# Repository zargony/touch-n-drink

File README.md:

# Touch 'n Drink

Touch 'n Drink is a small device that reads NFC id cards of club members of the [Aeroclub (LSC) Hamm][LSC Hamm] and allows to pay for items like cold drinks offered at the clubhouse. Purchases are forwarded to accounting so members pay via their regular monthly invoices. We're located at airfield [EDLH] in Hamm, Germany.

## Features

- Fetches authorized users and list of articles for sale from [Vereinsflieger] API
- Allows users to identify with NFC tag or id card and purchase articles
- Optional event tracking using [Mixpanel] for usage analytics
- Connects to 2.4 GHz WPA2/WPA3 Wifi (IPv4, DHCP)
- Simple numeric keypad and large, bright OLED display
- Power supply using standard USB-C cable (PD not required)
- Ergonomically priced and widely available hardware components
- Magnetic wall mount

## Hardware

ESP32-C3, Keypad, OLED Display and NFC reader in a custom acrylic case. See [hardware] folder for details.

## PCB

Small custom PCB for the microcontroller and connectors to other components. Either manufactured or manually soldered to a perfboard. See [pcb] folder for details.

## Firmware

Written in [Rust]. See [firmware] folder for details.

## Contributions

If you like this project, want to use it at your club, or if you want to discuss ideas and suggestions, feel free to start a [discussion][discussions] or open an [issue][issues]. Feel free to fork this repository and base your work upon it. Please open a pull request if your changes or features are useful to a broad audience.

## License

Hardware licensed under the [CERN Open Hardware License (Strongly Reciprocal)][OHL]. Software licensed under the [European Union Public License (EUPL)][EUPL]. Unless you explicitly state otherwise, any contribution intentionally submitted for inclusion in the work by you, shall be licensed as above, without any additional terms or conditions.

[hardware]: ./hardware
[firmware]: ./firmware
[pcb]: ./pcb

[discussions]: https://github.com/zargony/touch-n-drink/discussions
[issues]: https://github.com/zargony/touch-n-drink/issues

[EDLH]: https://skyvector.com/airport/EDLH/Hamm-Lippewiesen-Airport
[EUPL]: https://interoperable-europe.ec.europa.eu/collection/eupl/eupl-text-eupl-12
[LSC Hamm]: https://flugplatz-hamm.de
[Mixpanel]: https://mixpanel.com
[OHL]: https://cern-ohl.web.cern.ch/home
[Rust]: https://www.rust-lang.org
[Vereinsflieger]: https://www.vereinsflieger.de

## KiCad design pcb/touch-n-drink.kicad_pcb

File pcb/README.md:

# Touch 'n Drink PCB

## Custom PCB

A custom PCB holds the ESP32-C3 Module, a buzzer and connectors to wire up display, keypad and NFC reader. The PCB is quite simple and easy to manufacture. Choose any manufacturer you like.

If you don't want to manufacture a PCB, it's also easily possible to wire up components on a perfboard (see below).

Soldered PCB:

Empty PCB:

Rendered PCB model:

PCB Layout:

### Components

- 60x40 mm custom 2-layer PCB
- 1x ESP32-C3 SuperMini
  ([AliExpress](https://s.click.aliexpress.com/e/_DdYM4t9)) <!-- https://www.aliexpress.com/item/1005005967641936.html -->
  ([Amazon](https://amzn.to/4bCXYxz)) <!-- https://www.amazon.de/iHaospace-ESP32-C3-Mini-Entwicklungboard-ESP32-C3FN4/dp/B0D1Y5CPLX -->
  ([Model](https://grabcad.com/library/esp32c3-supermini-1))
- 1x Passive buzzer, THT, 12085
- 1x S8550, SMT, TSOT-23 (or other generic NPN transistor, BEC pin ordering)
- 1x 1k resistor, SMT, 0805
- 2x 5k resistor, SMT, 0805
- 1x 4-pin JST PH header, SMT, horizontal, S4B-PH-SM4-TB
- 1x 5-pin JST PH header, SMT, horizontal, S5B-PH-SM4-TB
- 1x 7-pin JST PH header, SMT, horizontal, S7B-PH-SM4-TB

## Perfboard (optional, instead of PCB)

Instead of manufacturing a custom PCB, you can wire up components on a 60x40 mm perfboard.

### Components

- Prototype PCB 60x40
  ([AliExpress](https://s.click.aliexpress.com/e/_Ddm12Wr)) <!-- https://www.aliexpress.com/item/1005006665029598.html -->
  ([Amazon](https://amzn.to/4eYnoIY)) <!-- https://www.amazon.de/Akozon-Leiterplatte-Doppelseiten-Prototyping-Universal/dp/B0B3MJ3WJM -->
  ([Model](https://grabcad.com/library/pcb-prototype-60x40-1))
- ESP32-C3 SuperMini
  ([AliExpress](https://s.click.aliexpress.com/e/_DdYM4t9)) <!-- https://www.aliexpress.com/item/1005005967641936.html -->
  ([Amazon](https://amzn.to/4bCXYxz)) <!-- https://www.amazon.de/iHaospace-ESP32-C3-Mini-Entwicklungboard-ESP32-C3FN4/dp/B0D1Y5CPLX -->
  ([Model](https://grabcad.com/library/esp32c3-supermini-1))
- Passive buzzer module, 3.3V, active low
  ([AliExpress](https://s.click.aliexpress.com/e/_Dl2FWF1)) <!-- https://www.aliexpress.com/item/1005006316591026.html -->
  ([Amazon](https://amzn.to/3Y72Ibw)) <!-- https://www.amazon.de/Jopto-Passives-niedrigstufiges-Lautsprecher-Kompatibel/dp/B096ZWCG7F -->
  ([Model](https://grabcad.com/library/buzzer-module-fc-07-1))
- Connectors for wiring to front panel (optional)
- Wires for soldering

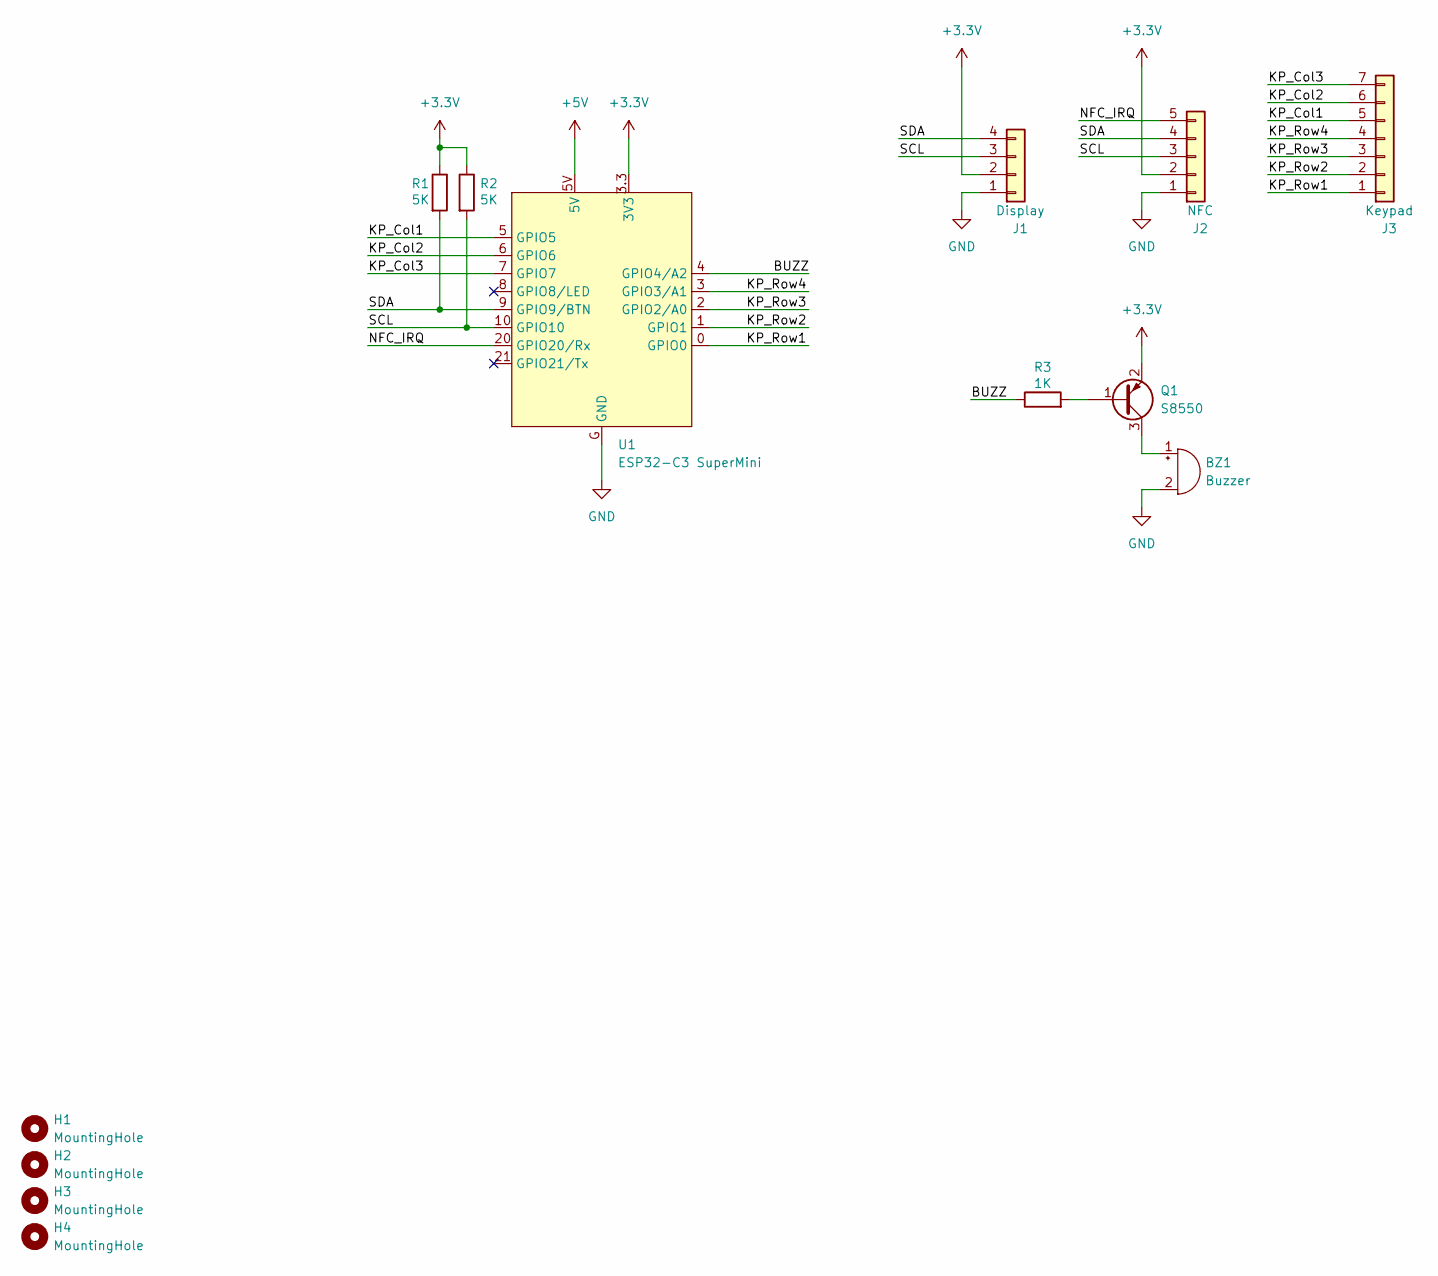
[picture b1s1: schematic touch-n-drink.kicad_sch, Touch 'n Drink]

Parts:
BZ1: Buzzer; MagneticBuzzer_ProSignal_ABT-410-RC
H1, H2, H3, H4: MountingHole; MountingHole_2.2mm_M2
J1: Display; JST_PH_S4B-PH-SM4-TB_1x04-1MP_P2.00mm_Horizontal
J2: NFC; JST_PH_S5B-PH-SM4-TB_1x05-1MP_P2.00mm_Horizontal
J3: Keypad; JST_PH_S7B-PH-SM4-TB_1x07-1MP_P2.00mm_Horizontal
Q1: S8550; TSOT-23
R1, R2: 5K; R_0805_2012Metric_Pad1.20x1.40mm_HandSolder
R3: 1K; R_0805_2012Metric_Pad1.20x1.40mm_HandSolder
U1: ESP32-C3 SuperMini; ESP32-C3_SuperMini

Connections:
+3.3V: J1.2, J2.2, Q1.2 (E), R1.1, R2.1, U1.3.3 (3V3)
+5V: U1.5V
/BUZZ: R3.1, U1.4 (GPIO4/A2)
/KP_Col1: J3.5, U1.5 (GPIO5)
/KP_Col2: J3.6, U1.6 (GPIO6)
/KP_Col3: J3.7, U1.7 (GPIO7)
/KP_Row1: J3.1, U1.0 (GPIO0)
/KP_Row2: J3.2, U1.1 (GPIO1)
/KP_Row3: J3.3, U1.2 (GPIO2/A0)
/KP_Row4: J3.4, U1.3 (GPIO3/A1)
/NFC_IRQ: J2.5, U1.20 (GPIO20/Rx)
/SCL: J1.3, J2.3, R2.2, U1.10 (GPIO10)
/SDA: J1.4, J2.4, R1.2, U1.9 (GPIO9/BTN)
GND: BZ1.2 (-), J1.1, J2.1, U1.G (GND)
unnamed: BZ1.1 (+), Q1.3 (C)
unnamed: Q1.1 (B), R3.2

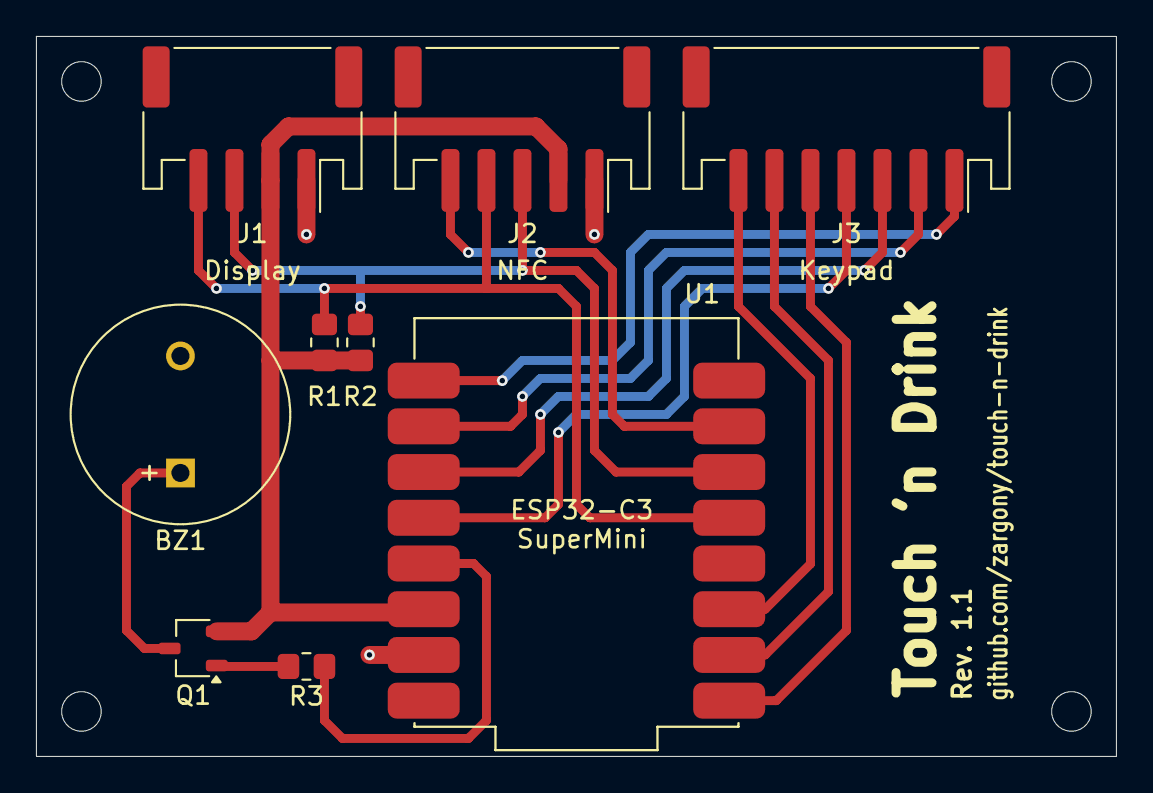
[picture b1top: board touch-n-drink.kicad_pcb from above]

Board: 2 copper layers, 60.0 x 40.0 mm, 13 parts (0 on the bottom side), 15 nets.

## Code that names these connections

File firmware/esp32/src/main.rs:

//! Touch 'n Drink Firmware
//!
//! Pinout ESP32-C3 Super Mini board
//!
//!                               | USB |
//! (Keypad Col1) A5/MISO/GPIO5 -  5 | 5V - 5V
//! (Keypad Col2)    MOSI/GPIO6 -  6 | G  - GND
//! (Keypad Col3)      SS/GPIO7 -  7 | 33 - 3V3
//!   (Board LED)     SDA/GPIO8 -  8 | 4  - GPIO4/A4/SCK (Buzzer)
//!     (I2C SDA)     SCL/GPIO9 -  9 | 3  - GPIO3/A3     (Keypad Row4)
//!     (I2C SCL)        GPIO10 - 10 | 2  - GPIO2/A2     (Keypad Row3)
//!     (NFC IRQ)     RX/GPIO20 - 20 | 1  - GPIO1/A1     (Keypad Row2)
//!                   TX/GPIO21 - 21 | 0  - GPIO0/A0     (Keypad Row1)
//!
//! Pinout OLED 2.42" Display
//!
//!            1   2   3   4
//!           GND VDD SCL SDA
//! GND - 1 |
//! VDD - 2 |
//! SCL - 3 |
//! SDA - 4 |
//!
//! Pinout 3x4 Matrix Keypad
//!
//!  1   2    3    4    5    6    7    8   9
//!  nc Col2 Row1 Col1 Row4 Col3 Row3 Row2 nc
//!
//! Pinout PN532 NFC Module
//!
//!             SCK MISO MOSI SS VCC GND IRQ RSTO
//!              1   2    3   4   5   6   7   8
//! GND - 1 |
//! VCC - 2 |
//! SDA - 3 |
//! SCL - 4 |
//!

#![no_std]
#![no_main]

mod buzzer;
mod config;
mod display;
mod keypad;
mod nfc;
mod pn532;
mod update;
mod wifi;

use alloc::boxed::Box;
use common::{GIT_SHA_STR, VERSION_STR};
use embassy_embedded_hal::shared_bus::asynch::i2c::I2cDevice;
use embassy_executor::Spawner;
use embassy_sync::{blocking_mutex::raw::NoopRawMutex, mutex::Mutex};
use embassy_time::{Duration, Timer};
use esp_backtrace as _;
use esp_hal::clock::CpuClock;
use esp_hal::efuse;
use esp_hal::gpio::{DriveMode, Input, InputConfig, Level, Output, OutputConfig, Pull};
use esp_hal::i2c::master::{BusTimeout, Config as I2cConfig, I2c};
use esp_hal::interrupt::software::SoftwareInterruptControl;
use esp_hal::peripherals::Peripherals;
use esp_hal::rng::Rng;
use esp_hal::rtc_cntl::{Rtc, RwdtStage};
use esp_hal::time::{Duration as EspDuration, Rate};
use esp_hal::timer::timg::TimerGroup;
use esp_println::println;
use esp_storage::FlashStorage;
use log::{debug, info, warn};

extern crate alloc;

esp_bootloader_esp_idf::esp_app_desc!();

/// Delay in seconds after which to restart on panic
#[cfg(not(debug_assertions))]
const PANIC_RESTART_DELAY: EspDuration = EspDuration::from_secs(10);
#[cfg(debug_assertions)]
const PANIC_RESTART_DELAY: EspDuration = EspDuration::from_secs(600);

/// Hardware watchdog timeout. RWDT will reset the system if not fed within this time.
const WATCHDOG_TIMEOUT: Duration = Duration::from_secs(10);

/// Custom halt function for esp-backtrace. Called after panic was handled and should halt
/// or restart the system.
#[unsafe(export_name = "custom_halt")]
unsafe fn halt() -> ! {
    unsafe {
        // System may be in any state at this time, thus everything is unsafe here. Stealing the
        // peripherals handle allows us to try to notify the user about this abnormal state and
        // restart the system. Any error should be ignored.
        let peripherals = Peripherals::steal();

        // TODO: Steal display driver and show a panic message to the user

        // Restart automatically after a delay
        println!("Restarting in {} seconds...", PANIC_RESTART_DELAY.as_secs());
        let mut rtc = Rtc::new(peripherals.LPWR);
        rtc.rwdt.set_timeout(RwdtStage::Stage0, PANIC_RESTART_DELAY);
        rtc.rwdt.unlisten();
        rtc.rwdt.enable();
        loop {
            esp_hal::riscv::asm::wfi();
        }
    }
}

#[embassy_executor::task]
async fn watchdog(mut rtc: Rtc<'static>) -> ! {
    debug!("Start watchdog task");

    // Enable watchdog
    rtc.rwdt.set_timeout(
        RwdtStage::Stage0,
        EspDuration::from_micros(WATCHDOG_TIMEOUT.as_micros()),
    );
    rtc.rwdt.listen();
    rtc.rwdt.enable();

    // Periodically feed watchdog
    let timeout = WATCHDOG_TIMEOUT / 2;
    loop {
        Timer::after(timeout).await;
        rtc.rwdt.feed();
    }
}

#[esp_rtos::main]
async fn main(spawner: Spawner) -> ! {
    let esp_config = esp_hal::Config::default().with_cpu_clock(CpuClock::max());
    let peripherals = esp_hal::init(esp_config);

    // Initialize global allocator
    esp_alloc::heap_allocator!(#[esp_hal::ram(reclaimed)] size: 64 * 1024);
    esp_alloc::heap_allocator!(size: 150 * 1024);

    // Initialize async executor
    let timg0 = TimerGroup::new(peripherals.TIMG0);
    let sw_int = SoftwareInterruptControl::new(peripherals.SW_INTERRUPT);
    esp_rtos::start(timg0.timer0, sw_int.software_interrupt0);

    // Initialize logging
    esp_println::logger::init_logger_from_env();
    info!("Touch 'n Drink v{VERSION_STR} ({GIT_SHA_STR})");

    // Initialize system devices
    let mut rng = Rng::new();
    let mut flash = FlashStorage::new(peripherals.FLASH);
    let _led = Output::new(peripherals.GPIO8, Level::High, OutputConfig::default());

    // Get device id (MAC address)
    let mut mac_address: const_hex::Buffer<6, false> = const_hex::Buffer::new();
    let device_id = mac_address.format_slice(efuse::base_mac_address().as_bytes());

    // Start feeding the watchdog
    let rtc = Rtc::new(peripherals.LPWR);
    debug!("Spawning watchdog task...");
    // Panic on failure since failing to spawn a task indicates a serious error
    spawner.spawn(watchdog(rtc).expect("Failed to spawn watchdog task"));

    // Read system configuration
    let config = config::read(&mut flash);

    // Initialize I2C controller
    let i2c_config = I2cConfig::default()
        // Standard-Mode: 100 kHz, Fast-Mode: 400 kHz
        .with_frequency(Rate::from_khz(400))
        // Reset bus after 24 bus clock cycles (60 µs) of inactivity
        .with_timeout(BusTimeout::BusCycles(24));
    let i2c = I2c::new(peripherals.I2C0, i2c_config)
        // Panic on failure since without I2C there's no reasonable way to tell the user
        .expect("I2C initialization failed")
        .with_sda(peripherals.GPIO9)
        .with_scl(peripherals.GPIO10)
        .into_async();

    // Share I2C bus. Since the mcu is single-core and I2C is not used in interrupts, I2C access
    // cannot be preempted and we can safely use a NoopMutex for shared access.
    let i2c: Mutex<NoopRawMutex, _> = Mutex::new(i2c);

    // Initialize display
    let mut display = display::Display::new(I2cDevice::new(&i2c))
        .await
        // Panic on failure since without a display there's no reasonable way to tell the user
        .expect("Display initialization failed");

    // Initialize keypad
    let keypad_input_config = InputConfig::default().with_pull(Pull::Up);
    let keypad_output_config = OutputConfig::default().with_drive_mode(DriveMode::OpenDrain);
    let mut keypad = keypad::Keypad::new(
        [
            Input::new(peripherals.GPIO5, keypad_input_config),
            Input::new(peripherals.GPIO6, keypad_input_config),
            Input::new(peripherals.GPIO7, keypad_input_config),
        ],
        [
            Output::new(peripherals.GPIO0, Level::High, keypad_output_config),
            Output::new(peripherals.GPIO1, Level::High, keypad_output_config),
            Output::new(peripherals.GPIO2, Level::High, keypad_output_config),
            Output::new(peripherals.GPIO3, Level::High, keypad_output_config),
        ],
    );

    // Initialize NFC reader
    let nfc_irq_input_config = InputConfig::default().with_pull(Pull::Up);
    let nfc_irq = Input::new(peripherals.GPIO20, nfc_irq_input_config);
    let mut nfc = nfc::Nfc::new(I2cDevice::new(&i2c), nfc_irq)
        .await
        // Panic on failure since an initialization error indicates a serious error
        .expect("NFC reader initialization failed");

    // Initialize buzzer
    let mut buzzer = buzzer::Buzzer::new(peripherals.LEDC, peripherals.GPIO4);

    // Initialize Wifi
    let wifi = wifi::Wifi::new(
        rng,
        peripherals.WIFI,
        spawner,
        config.wifi_country,
        &config.wifi_ssid,
        &config.wifi_password,
    )
    // Panic on failure since an initialization error indicates a static configuration error
    .expect("Wifi initialization failed");

    // Initialize firmware updater
    let mut updater_buffer = [0; update::BUFFER_SIZE];
    let mut updater = match update::Updater::new(&mut flash, &mut updater_buffer) {
        Ok(updater) => Some(updater),
        Err(err) => {
            warn!("Firmware updates unavailable: {err}");
            None
        }
    };

    // Run firmware
    let devices = common::Devices {
        rng: &mut rng,
        display: &mut display,
        keypad: &mut keypad,
        nfc: &mut nfc,
        buzzer: &mut buzzer,
        network: &wifi,
        updater: updater.as_mut(),
    };
    Box::pin(common::run(&config, device_id, devices)).await
}

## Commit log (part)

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2024-07-07 Initial description and hardware components list
2024-07-09 Add 3d models of hardware components
2024-07-09 Add case and components assembly
2024-07-10 Initial blinky firmware
2024-07-10 Add simple Wifi interface with dummy function scanning for access points
2024-07-11 Start using embassy-executor for async runtime
2024-07-11 Switch to more actively maintained SSD1306 driver which is SSD1309 compatible
2024-07-12 Update list of components and shop links
2024-07-12 Improve side spacer width and PCB placement
2024-07-12 Improve case cable hole and add cable strain release
2024-07-14 Adjust back plate mounting holes
2024-07-14 Switch from SPI to I2C for display and upcoming devices
2024-07-15 Don't refresh hello screen when idle
2024-07-15 Use markdown link references
2024-07-19 Add front plate engraving
2024-07-20 Fix error for missing libtest harness (can't find crate for `test`) by disabling the unit test runner for now
2024-07-20 Add cargo data caching to CI workflow
2024-07-22 Strip lsc prefix from name and url
2024-07-22 Upload build artifact of CI runs
2024-07-23 Update front plate engravings
2024-07-25 Add images to hardware description
2024-07-25 Pass key arguments by value since it's a small, copyable type
2024-08-07 Switch to new VScode crates extension
2024-08-10 Fix and describe log filter configuration
2024-08-10 Add esp-wifi configuration to set Wifi country code to Germany
2024-08-10 Derive Clone and Debug and rename variants of keypad driver error
2024-08-10 Distinguish between Wifi initialization and runtime errors
2024-08-10 Build esp-wifi with release optimizations as it recommends
2024-08-10 Show git short sha on splash screen
2024-08-10 Refactor display text output
2024-08-10 Move version string constants to root module
2024-08-10 Refactor user interface to a separate module
2024-08-12 Use u8g2 fonts
2024-08-12 Refactor common screen footer
2024-08-17 Implement main user interface flow
2024-08-18 Log start and success of device initialization
2024-08-19 Use shared I2C bus
2024-08-19 Add image of assembled device
2024-08-20 Pass screens by reference
2024-08-22 Make I2C bus sharing construction more obvious
2024-08-22 Add custom halt function that restarts the system after a delay
2024-08-22 Disable noisy esp-wifi logging
2024-08-26 Add passive buzzer driver
2024-08-26 Improve logging of user interface main flow
2024-08-26 Reduce NFC read sleep time for quicker response to id card scans
2024-08-27 Switch to async I2C
2024-08-27 Add Logo in pixil format (source of bi-color image for splash screen)
2024-08-29 Add license
2024-08-31 Refactor custom pn532 driver
2024-08-31 Refactor pn532 process function with timeout
2024-09-04 Fix Keypad wiring typo
2024-09-04 Update to esp-hal 0.20 and update dependencies
2024-09-04 Update readme and add changelog
2024-09-04 Remove obsolete comment about async I2C
2024-09-09 Remove unneeded async from buzzer drive function
2024-09-09 Switch clippy to pedantic and fix some warnings
2024-09-10 Don't disable debug-assertions for esp-wifi
2024-09-14 Add Wifi network stack with IPv4 DHCP autoconfiguration
2024-09-22 Update dependencies
2024-09-23 Indicate debug version in splash screen
2024-09-24 Pass Wifi to UI and wait for network to come up
2024-09-24 Remove unneeded dereferences in match statements
2024-09-24 Refactor error types
2024-09-24 Add support to query DNS
2024-09-26 On error, wait at least 1s without responding to keypad
2024-09-27 Provide global memory allocator with esp-alloc
2024-09-27 Turn off esp-wifi overflow checks as they seem to cause random panics
2024-09-27 Use 72 KB heap for global allocator (like esp-rs examples recommend)
2024-09-28 Read system configuration from flash partition
2024-09-30 Remove StaticCell in favour of using boxed allocations
2024-10-01 Provide convenient network type aliases, static DNS socket and TCP client
2024-10-02 Remove generics from HTTP client
2024-10-04 Asynchronous streaming JSON parser
2024-10-04 Allow to deserialize JSON Value types
2024-10-04 Refactor JSON reader tests
2024-10-04 Asynchronous streaming JSON writer
2024-10-04 Pass HID resources as references to UI flow
2024-10-05 Improve JSON reader value handling
2024-10-05 Use streaming JSON for HTTP bodies
2024-10-06 Use streaming JSON for reading system configuration, remove serde dependencies
2024-10-06 Refactor streaming JSON to separate modules
2024-10-07 Refactor JSON raw writing
2024-10-07 Allow any supported type when reading JSON array elements or object values
2024-10-07 Allow JSON object and array reader closures to return results
2024-10-09 Improve JSON streaming reading of arrays and objects
2024-10-10 Fix JSON parsing of empty arrays or objects
2024-10-10 Adjust buzzer volume
2024-10-10 Add clone and eq traits to error types
2024-10-10 Basic Vereinsflieger API client
2024-10-14 Create PCB design
2024-10-14 Add PCB information, rearrange hardware README
2024-10-15 Move PCB design to a separate folder
2024-10-17 Add GitHub URL and QR to front plate engravings, avoid duplicate vector paths
2024-10-17 Add hardware (case) changelog
2024-10-18 Fix clippy warning in Rust 1.82
2024-10-19 Refactor http client and connection for better lifetime handling
2024-10-19 Allow unsized context types in JSON array and object deserialization
2024-10-21 Refactor Vereinsflieger API client to separate modules
2024-10-22 Fetch article names and prices from Vereinsflieger
2024-10-25 Support unencrypted Wifi connections by setting no password
2024-10-25 Use separate config data partition, also prepare OTA partitions
2024-10-25 Improve buzzer sounds, add deny tone
2024-10-27 Add feature to enable additional logging of dependencies
2024-10-27 Better handling of startup initialization and error
2024-10-27 Improve visibility of user flow errors in logs
2024-10-27 Fix HTTP pipelined requests failing after incompletely reading a response body
2024-10-28 Fetch users from Vereinsflieger
2024-10-29 Make articleid a String, like Vereinsflieger defines it
2024-10-29 Extract current time from HTTP responses and keep track of it
2024-10-29 Fix broken JSON reader test
2024-10-29 Reorganize font size and title alignments
2024-10-29 Release 0.1.0
2024-11-04 Add GitHub release action workflow
2024-11-04 Increase heap memory to 100k
2024-11-04 Refactor Wifi connection loop
2024-11-09 Refactor screen positioning
2024-11-26 Fix typo
2024-11-26 Use anonymous lifetime where no reference to it is needed
2024-11-26 Pass HTTP client to API client only when a connection needs to be established
2024-11-27 Release 0.2.0
2024-11-28 Refactor time module for easier integration with Instant types
2024-12-04 Refactor idle timeout handling
2024-12-04 Accept any timezone when setting current time
2024-12-06 Implement simple daily schedule to refresh articles and users
2024-12-10 Use const-hex create instead of hex
2024-12-10 Allow JSON object values to be built from referenced key strings
2024-12-19 Refactor static version string
2024-12-19 Rename http connection variable for name deduplication
2024-12-19 Support to write NFC uids directly to JSON
2024-12-20 Add list of main features to README
2024-12-21 Add telemetry tracking of errors
2024-12-22 Revert failure screen to be generic over any displayable message again
2024-12-24 Remove useless prefixes from API client error messages
2025-01-19 Reduce stack size and silence clippy warning by allocating http buffers on heap
2025-01-19 Increase heap memory to 150k
2025-01-19 Refactor left and right aligned text on screen
2025-01-20 Use expect() instead of verbose match/panic expressions
2025-01-20 Allow to configure multiple article ids (but still use the first one only for now)
2025-01-21 Refactor screen text trimming
2025-01-22 Improve vertical spreading of article selection list, allowing up to 4 articles now
2025-01-22 Better Articles::get ergonomics
2025-01-22 Show article name and price when asking to select amount
2025-01-22 Release 0.3.0
2025-01-22 Fix Cargo.toml formatting
2025-01-24 Increase NFC buffer size. Fixes "buffer too small" errors with some cards
2025-01-24 Trim "Getränk/e" prefix from article description when displaying
2025-01-24 Support decoding numeric HTML entities in JSON strings
2025-02-05 Fix max NFC response length
2025-03-31 Don't preset toolchain components, except for needed target architecture
2025-05-04 espflash write-bin now also accepts a partition name as address
2025-06-30 Add OHL-S / EUPL licensing
2025-09-14 Fix clippy::uninlined-format-args warning introduced in Rust 1.88
2025-09-16 Update GitHub actions
2025-09-16 Flag config partition as read-only
2025-09-16 Use espflash 4.x.x
2025-09-24 Remove workaround for espflash 4.0.x
2025-09-24 Enable system hardware watchdog (RWDT) to recover from unresponsive states
2025-09-25 Detect HTTP redirects
2025-09-25 Refactor HTTP request handling
2026-02-27 Update to latest esp-* and embassy-* crates
2026-02-27 Really turn off LEDC driving when not needed
2026-02-28 Update to Rust Edition 2024
2026-03-10 Use cargo install --locked to install build tools with known working dependencies
2026-03-10 Replace custom JSON (de)serialization with serde and serde_json
2026-03-11 Update GitHub CI actions
2026-03-11 Add more user greetings
2026-03-11 Use unsigned integers for widths and heights
2026-03-11 Trim generic article name prefixes globally
2026-03-11 Refactor user greeting
2026-03-12 Create one aggregated checksum file for releases instead of multiple ones
2026-03-12 Rename partition and flash region related variables
2026-03-13 Pass reference of flash storage for reading system configuration
2026-03-14 Rename json module to reader
2026-03-14 Add LineReader
2026-03-15 Use boxed slices instead of vecs
2026-03-15 Update partition table layout and config partition type
2026-03-16 Add simple OTA updater using GitHub releases
2026-03-16 Add timeout handling to OTA http requests
2026-03-16 Add OTA update check to daily schedule
2026-03-16 Skip OTA update checks in debug builds
2026-03-16 Release 2.0.0
2026-03-19 Refactor Mixpanel API client to make it more generic
2026-03-19 Refactor Vereinsflieger API client to make it more generic
2026-03-19 Adjust OTA http method helper
2026-03-19 Properly parse and filter article, sale and user dates
2026-03-20 Refactor article and user updating
2026-03-26 Implement DrawTarget for Display
2026-03-27 Switch to embassy Duration type in main
2026-03-28 Remove keypad::Key and return char instead
2026-03-28 Add rectangle helper utils
2026-03-31 Try to parse Vereinsflieger error response for a more detailed error message
2026-03-31 Submit telemetry when initialization fails
2026-04-08 Add NFC UID tests
2026-04-08 Move buzzer methods to buzzer interface trait
2026-04-09 Add Zed editor settings
2026-04-09 Log warning when automatic OTA update is unavailable
2026-04-10 Increase OTA download timeout
2026-04-10 Don't sort sha256sums
2026-04-10 Submit telemetry when displaying an error
2026-04-10 Clean up use of workspace dependencies
2026-04-11 Release 2.0.2
2026-04-13 Move frontend/backend resource building to common crate
2026-04-15 Change article indexing to ignore missing and unwanted articles
2026-04-15 Move construction of platform-independent resources to common crate
2026-04-15 Remove Articles::get_by_index(), add tests for Articles::iter()
2026-04-15 Refactor xtask chip value enum
2026-04-15 Rename xtask Command enum to MainCommand
2026-04-16 Fix visibility of internal types and satisfy Rust 1.95 clippy
2026-04-17 Fix bug which missed expired Vereinsflieger accesstoken and and didn't refresh
2026-04-18 Update package author
2026-04-19 Remove unneeded dependencies from esp32 crate
2026-04-19 Clean up xtask argument handling
2026-04-19 Export only externally needed types from common crate
2026-04-23 Use a task for automatic telemetry submission in background
2026-04-23 Use exponential backoff retrying to submit telemetry
2026-04-23 Release 2.0.4
